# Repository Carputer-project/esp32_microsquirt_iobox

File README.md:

# ESP32 MicroSquirt I/O box

DIY clone of the official MicroSquirt "I/O-box" — an **ESP32 + SN65HVD230** that
listens to the MS2/Extra MicroSquirt CAN realtime broadcast (base ID `0x5F0`,
500 kbps) and drives **fan**, **idle control (IAC)** and **6 generic low-side
outputs**, with the same fail-safe the real I/O-box uses (outputs off when CAN
goes silent).

Because MS2/Extra has no I/O-box slave protocol (that's an MS3-only feature), this
box is an **autonomous "smart slave"**: it computes its own output logic from the
broadcast data. It also implements the full **Megasquirt 29-bit expansion
protocol** as a responder (so an MS2/Extra master *can* drive its outputs/ADC
directly), and broadcasts a small **`0x710`** frame for the in-dash HMI.

Works with **any MS2/Extra 3.4.x MicroSquirt V3** — no fuel/spark tune changes
needed, only CAN broadcast settings.

## Features

- **Fan** — CLT hysteresis (on ≥ 200 °F / off ≤ 190 °F default, adjustable) or
  manual override, driven through a ULN2003A channel (default O6/GPIO23).
- **IAC** — 30 Hz PWM on GPIO32 → IRLZ44N → 3-wire rotary ISCV. Three modes:
  **Auto** (CLT warm-up table + RPM trim), **Follow** (mirror the ECU's own
  `iacstep` → fully TunerStudio-tunable closed-loop idle), or **Manual**.
- **O1–O6** — generic low-side outputs (ULN2003A): manual, CLT-temp or RPM
  trigger. O1 defaults to a 7000 rpm shift light.
- **Inputs drive outputs** — A1–A4 analog (0-5 V, 0.15 V hysteresis) can force any
  output or the fan (I/O-box parity).
- **29-bit CAN responder** — MS2/Extra remote-port protocol: MSG_REQ/MSG_CMD on
  table 7; remote idle PWM, remote on/off outputs, remote boost, ADC readback.
- **`0x710` dash broadcast** — A1–A4 threshold latches for
  the in-dash HMI (indicator/high-beam/brake icons). 10 Hz, always on.
- **GC9A01A round gauge** — 1.28" 240×240 idle-control display: big IAC duty %,
  RPM / target RPM / CLT / idle mode, fan + CAN status line.
- **Fail-safe** — all outputs off after 500 ms without CAN (matches the real
  I/O-box); IAC falls back to the ~1000-1200 rpm valve default.
- **Persistent config** — all settings stored in NVS; loadable/settable over
  serial or via the included Windows diagnostic app.

## Repo layout

```
esp32_microsquirt_iobox/
├── firmware/            PlatformIO ESP32 firmware — iobox2 (round display)
├── firmware-v3/         PlatformIO ESP32 firmware — iobox3 (configurable pins, display opt-in)
├── pcb/                 KiCad 8 PCB design (iobox2: schematic, board, project)
├── diag/                iobox_diag.py — Windows test/configure app (Python + Tkinter)
└── docs/
    ├── OPERATION.md     How the box works + how to use it (modes, commands, display)
    ├── PROTOCOL.md      CAN protocol reference (0x5F0 broadcast, 0x710, 29-bit responder)
    ├── BUILD.md         Full point-to-point build/wiring guide
    └── PARTS.md         Parts list with rough prices
```

## Two firmware variants

| | `firmware/` (iobox2) | `firmware-v3/` (iobox3) |
|---|---|---|
| Board | ESP32 DevKit + breakout, GC9A01A round display | Bare ESP32-WROOM-32 module board, 7" dash on CAN is the HMI |
| IAC pin | 32 (compile-time) | **runtime-configurable** (`P` command / diag app Pins tab) |
| Outputs | O1-O6 = 25,26,27,14,13,23 (compile-time) | O1-O7 = 13,12,14,27,26,25,33 default, **runtime-configurable** |
| Round display | yes | opt-in (`P TFT 1`; GPIO19 conflicts with IAC) |
| Switches | none (removed) | none |
| Use `P`? | no (fixed pins) | yes |

Both share the same core (CAN broadcast decode, fan, IAC, outputs, engine
profile warnings, 29-bit responder, `0x710` dash broadcast). iobox2 = one build
for that board; iobox3 = one firmware, pin map set once per board via the
diag app.

## Quick start

1. **Build hardware** — see `docs/BUILD.md` (wiring) and `docs/PARTS.md` (parts).
   The KiCad design in `pcb/` is the iobox2 board; the point-to-point
   build guide is an alternative for module wiring without a PCB. iobox3 is the
   bare-module 3×3 board — see `firmware-v3/README.md`.
2. **Flash firmware** (pick the folder matching your board):

   ```sh
   cd firmware        # iobox2  — or:  cd firmware-v3  for iobox3
   pio run                 # build
   pio run --target upload # flash over USB
   pio device monitor -b 115200
   ```

   Requires PlatformIO (ESP32 Arduino framework). At the serial prompt type `?`
   for a live status dump. On iobox3, type `P` to see the pin map (set it once
   from the diag app's Pins tab if your board is wired differently).
3. **Configure the MicroSquirt (one time)** in TunerStudio → CAN Realtime Data
   Broadcasting: **On**, base ID **1520**, rate **20 Hz**, enable groups
   **00** (rpm), **02** (baro/map/mat/clt), **03** (tps/batt/afr), and optionally
   **06** (iacstep) for Follow mode. Details in `docs/OPERATION.md`.
4. **Use the Windows app** (`diag/iobox_diag.py`) to set fan thresholds, IAC mode,
   output triggers, input mappings, the 29-bit responder and (iobox3) the pin map
   from a GUI.

## Hardware snapshot

| GPIO | Function | Drives |
|------|----------|--------|
| 5 / 4 | CAN TX / RX | SN65HVD230 (MicroSquirt pins 2/3, CANH/CANL) |
| 32 | IAC PWM (30 Hz) | ISCV via IRLZ44N |
| 25,26,27,14,13,23 | O1–O6 | ULN2003A (O6 = fan by default, `Y<k>` to change) |
| 2 | Status LED | onboard (CAN heartbeat / fail-safe blink) |
| 36,39,34,35 | A1–A4 analog 0-5 V | 10k/20k divider (or PCB 12 V→3.3 V dividers) |
| 15,21,22,19 | GC9A01A round display | SCLK / MOSI / CS / DC |

All outputs are **low-side (ground-switching)**, like the real MS I/O-box. Never
feed 12 V into the ESP32 or SN65HVD230 — a 12 V→5 V buck is mandatory.

## Serial command cheat sheet

| Command | Effect |
|---------|--------|
| `?` | status dump |
| `F205` / `F1` / `F0` | fan auto @205 °F / manual on / off |
| `E190` | fan off hysteresis 190 °F |
| `I35` / `I` / `I F` | IAC manual 35% / auto / follow-ECU |
| `T900` | idle target 900 rpm (auto mode) |
| `S7000` | shift light @7000 rpm |
| `O3 R3500` / `O4 1` | O3 above 3500 rpm / O4 on |
| `A1 O2 3.5` / `A2 F 2.0` | analog threshold → output/fan |
| `Y6` | fan on ULN channel 6 |
| `R1` / `R0` / `RB5` | 29-bit responder on/off / box ID |
| `W1` / `W0` | engine profile monitoring on/off |
| `W idle 650 1000` | idle RPM band (warning below/above, <20% TPS) |
| `W clt 230` / `W mat 160` | max coolant / intake °F |
| `W batt 11.0 16.0` / `W map 280` | battery band / max MAP kPa |
| `W afr 10.0 16.5` | AFR window (below=RICH, above=LEAN) |
| `W hold 3000` / `W warnout 3` | warn latch ms / blink O3 as check-engine lamp |
| `P IAC 19` / `P O3 27` | **iobox3 only** — set IAC / output pin |
| `P RESET` | iobox3 only — restore default pin map |
| `S` | full command list |

## CAN at a glance

- **ECU → box**: 11-bit IDs `0x5F0`–`0x5F8` (group N at ID 1520+N), big-endian,
  8 bytes/group, 20 Hz. rpm@6, baro/map/mat/clt@16-22 (×0.1), tps/batt/afr@24-28
  (×0.1), iacstep@54 (×0.392 = duty %).
- **Box → dash**: `0x710`, byte0 = A1–A4 latches, byte1 = reserved, byte2 = counter.
- **Master → box**: 29-bit extended `MSG_REQ`/`MSG_CMD` (MS2/Extra remote ports).

Full byte maps and the 29-bit responder spec: `docs/PROTOCOL.md`.

## Project context

Built for a 7A-GTE (7A block + 4A-GE head) MicroSquirt V3 car: the I/O box frees
the ECU's FIDLE (moving boost control off it), adds proper PWM idle via the ISCV,
handles the radiator fan, and feeds warning-lamp states (indicators, high beam,
brake) to a 7" ESP32-S3 in-dash HMI. This box is one of several open-source
modules in the [Carputer-project](https://github.com/Carputer-project)
ecosystem.

## License

Firmware, PCB and tooling in this repo are released for personal/DIY use.
See each file header for notes.

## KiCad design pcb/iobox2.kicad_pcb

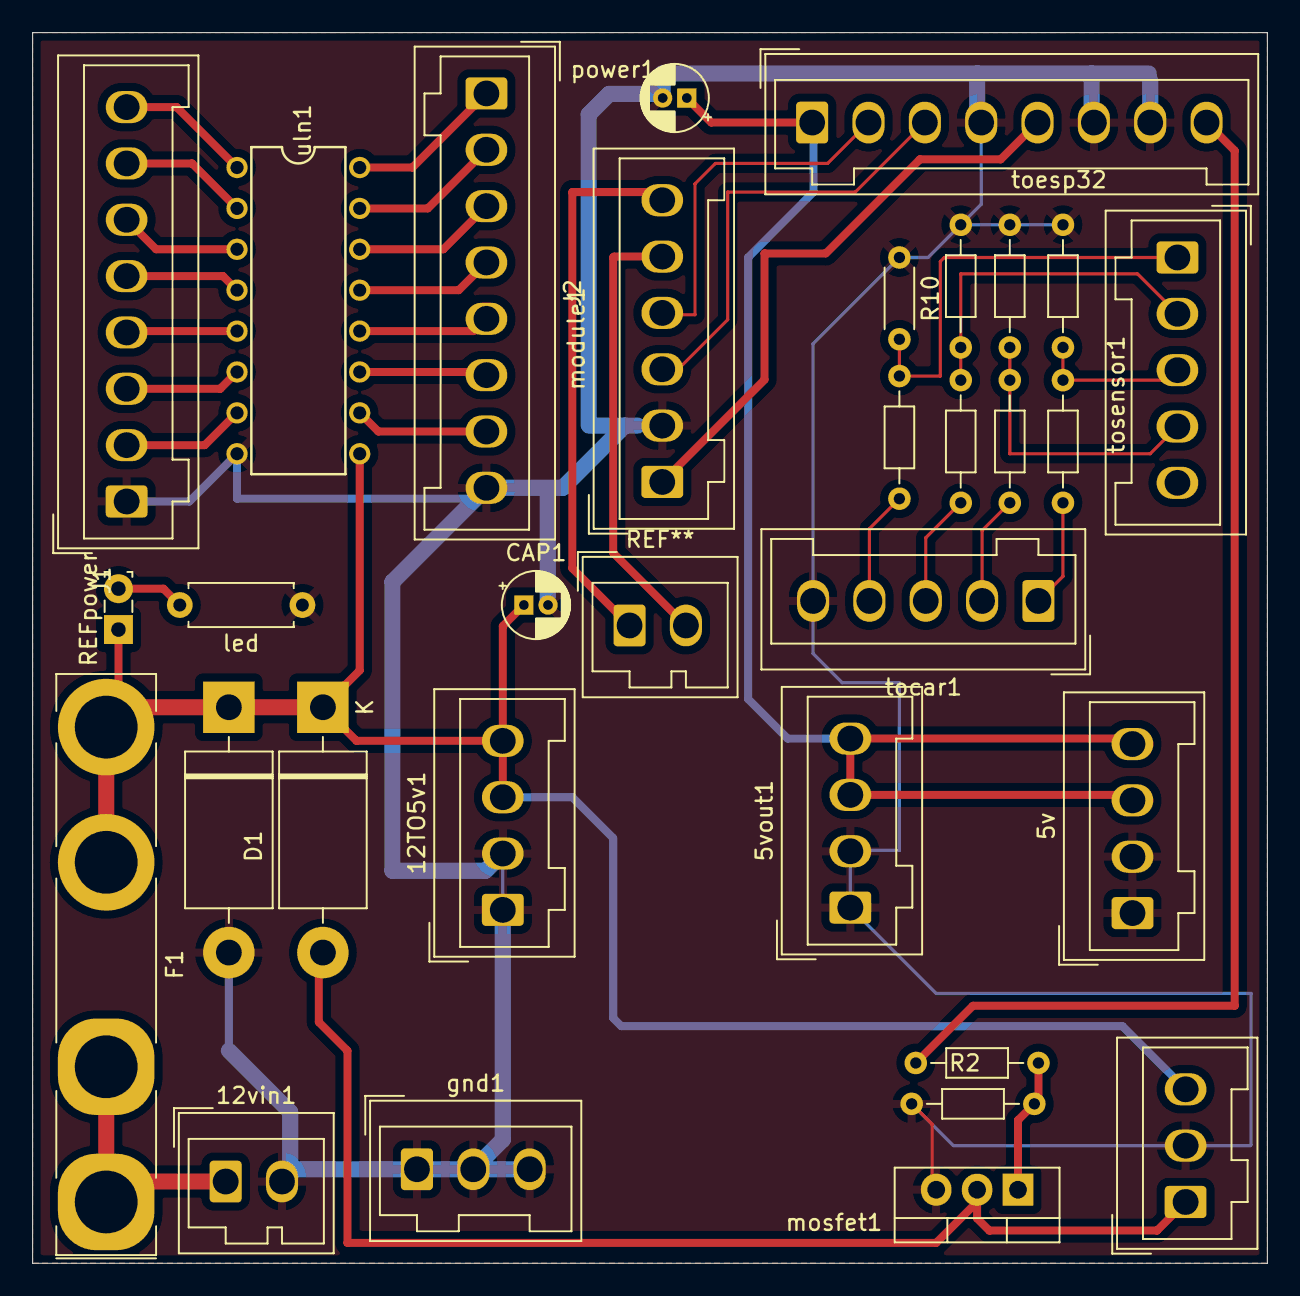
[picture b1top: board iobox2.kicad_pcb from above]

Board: 2 copper layers, 76.7 x 76.5 mm, 31 parts (0 on the bottom side), 32 nets.

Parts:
5v: 5v; Wago_734-134_1x04_P3.50mm_Vertical
5vout1: 5vout; Wago_734-134_1x04_P3.50mm_Vertical
12TO5v1: 12v-5v; Wago_734-134_1x04_P3.50mm_Vertical
12vin1: 12v in; Wago_734-132_1x02_P3.50mm_Vertical
CAP1: CAP; CP_Radial_D4.0mm_P1.50mm
D1, D2: 1N5404; D_DO-201AD_P15.24mm_Horizontal
F1: Fuse; Fuseholder_Keystone_3555-2
IDLE1: IAC; Wago_734-133_1x03_P3.50mm_Vertical
J1, J2: Conn_01x08; Wago_734-138_1x08_P3.50mm_Vertical
R1, R2, R3, R4, R5, R6, R7, R8, R9: R; R_Axial_DIN0204_L3.6mm_D1.6mm_P7.62mm_Horizontal
R10: R; R_Axial_DIN0204_L3.6mm_D1.6mm_P5.08mm_Horizontal
REFpower: led; LED_SideEmitter_Rectangular_W4.5mm_H1.6mm
gnd1: gnd; Wago_734-133_1x03_P3.50mm_Vertical
led: lr; R_Axial_DIN0207_L6.3mm_D2.5mm_P7.62mm_Horizontal
module1: canbus; Wago_734-136_1x06_P3.50mm_Vertical
mosfet1: IRLZ44N; TO-220-3_Vertical
power1: capp; CP_Radial_D4.0mm_P1.50mm
tocar1: CAR; Wago_734-135_1x05_P3.50mm_Vertical
toesp32: ESP32; Wago_734-138_1x08_P3.50mm_Vertical
tosensor1: sensor; Wago_734-135_1x05_P3.50mm_Vertical
uln1: ULN2002A; DIL16

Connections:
+3.3V: module1.1, toesp32.5
+5V: 5v.3, 5v.4, 5vout1.3, 5vout1.4, power1.1, toesp32.1
GND: 5v.1, 5v.2, 5vout1.1, 5vout1.2, 12TO5v1.1, 12TO5v1.2, 12vin1.2, CAP1.2, D1.2 (A), IDLE1.2, J1.1, J2.8, R1.2, R4.1, R6.1, R8.1, R10.1, gnd1.1, gnd1.2, gnd1.3, led.1, module1.2, mosfet1.3 (S), power1.2, tocar1.5, toesp32.4, toesp32.6, toesp32.7, uln1.8 (GND)
unnamed: 12TO5v1.3, 12TO5v1.4, CAP1.1, D1.1 (K), D2.1 (K), F1.2, IDLE1.3, REFpower.1, uln1.9 (COM)
unnamed: 12vin1.1, F1.1
unnamed: D2.2 (A), IDLE1.1, mosfet1.2 (D)
unnamed: J1.2, uln1.7 (I7)
unnamed: J1.3, uln1.6 (I6)
unnamed: J1.4, uln1.5 (I5)
unnamed: J1.5, uln1.4 (I4)
unnamed: J1.6, uln1.3 (I3)
unnamed: J1.7, uln1.2 (I2)
unnamed: J1.8, uln1.1 (I1)
unnamed: J2.1, uln1.16 (O1)
unnamed: J2.2, uln1.15 (O2)
unnamed: J2.3, uln1.14 (O3)
unnamed: J2.4, uln1.13 (O4)
unnamed: J2.5, uln1.12 (O5)
unnamed: J2.6, uln1.11 (O6)
unnamed: J2.7, uln1.10 (O7)
unnamed: module1.3, toesp32.3
unnamed: module1.4, toesp32.2
unnamed: R1.1, R2.1, mosfet1.1 (G)
unnamed: R3.2, tocar1.1
unnamed: R5.2, tocar1.2
unnamed: R7.2, tocar1.3
unnamed: R9.2, tocar1.4
unnamed: R2.2, toesp32.8
unnamed: R9.1, R10.2, tosensor1.1
unnamed: R7.1, R8.2, tosensor1.2
unnamed: R3.1, R4.2, tosensor1.3
unnamed: R5.1, R6.2, tosensor1.4
